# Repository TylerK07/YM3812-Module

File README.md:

# YM3812-Module
This code repository parallels a series of articles about a YM3812 module written on thingsmadesimple.com

With each new article, the functionality of the module will grow, and the associated code and schematics will be available here.

<hr/>

## Current Articles

### <a href='https://www.thingsmadesimple.com/2022/11/28/ym3812-part-1-register-basics/'>YM3812 Part 1: Register Basics</a>
Focuses on FM Synthesis basics, the YM3812's register map and electrically controlling the chip's pins.

### <a href='https://thingsmadesimple.com/2023/01/02/ym3812-part-2-face-reveal/'>YM3812 Part 2: FACE Reveal</a>
Introduces a basic implementation of the YM3812 circuit controlled by an AVR128DA28 microcontroller that we will build on in future articles. Think of it as a "Hello World" starting point that ensure the circuit works and that we can upload code to the microcontroller.

### <a href='https://www.thingsmadesimple.com/2023/01/21/ym3812-part-3-behind-the-code/'>YM3812 Part 3: Behind the Code</a>
Walks through the implementation of the YM3812 class used in Part 2 and describes how each of the register manipulation functions work.

### <a href='https://www.thingsmadesimple.com/2023/02/11/ym3812-part-4-midi-journey/'>YM3812 Part 4: MIDI Journey</a>
Adds a MIDI input to our schematic, and discusses how to translate MIDI note numbers into frequencies the YM3812 understands

### <a href='https://www.thingsmadesimple.com/2023/03/05/ym3812-part-5-midi-polyphony/'>YM3812 Part 5: MIDI Polyphony</a>
Adds Polyphony to our breadboard module, walking through a couple of algorithms in the process.

### <a href='https://www.thingsmadesimple.com/2023/04/29/ym3812-part-6-patches/'>YM3812 Part 6: Patches</a>
Revise the YM3812 class implementation to support more generic instrument definition

### <a href='https://www.thingsmadesimple.com/2023/05/13/ym3812-part-7-percussive-maintenance/'>YM3812 Part 7: Percussive Maintenance</a>
Add General MIDI drum support by linking different drum sounds to different notes on the keyboard

### <a href='https://www.thingsmadesimple.com/2023/05/30/ym3812-part-8-velocity-sensitivity/'>YM3812 Part 8: Velocity Sensitivity</a>
Add touch sensitivity to the module by selectively scaling the right operator levels

### <a href='https://www.thingsmadesimple.com/2023/07/28/ym3812-part-9-synth-card/'>YM3812 Part 9: SynthCard</a>
Turn that breadboard into a business card sized PCB!

### <a href='https://www.thingsmadesimple.com/2023/09/02/ym3812-part-10-pitch-bend/'>YM3812 Part 10: Pitch Bend</a>
Add pitch bend capabilities and shred on a YM3812

<hr/>

## Article Backlog:

### YM3812 Part ?: OPL2 in STEREO!
Add another YM3812 chip and some stereo effects for panning and detuning

### YM3812 Part ?: Adding a menu to swap patches
Add a TFT Screen and a Rotary Encoder so we can adjust patch assignments to MIDI channels

### YM3812 Part ?: Adjust Patch Properties
Add buttons and a menu system that lets us adjust patch settings individually

### YM3812 Part ?: Visualizing 2-OP envelopes
Add a graphical visualization that helps us interpret patch settings

### YM3812 Part ?: Virtual 4-OP Voices
Add support for virtual four-operator voices

and more...

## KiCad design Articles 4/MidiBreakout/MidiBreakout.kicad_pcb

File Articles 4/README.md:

### <a href=''>YM3812 Part 4: MIDI Journey</a>
This article introduces the circuitry and functionality necessary to implement MIDI on the YM3812 module. This article especially focuses on translating note frequencies between MIDI note codes and the block / F-Number properties used by the YM3812. To demonstrate how the translation function and basic MIDI handlers work, this code implements a monophonic midi algorithm that plays all incoming notes on channel zero of the YM3812.

<hr/>

### Schematic
The schematic folder includes adds MIDI functionality to the basic schematic used in articles 1-3.

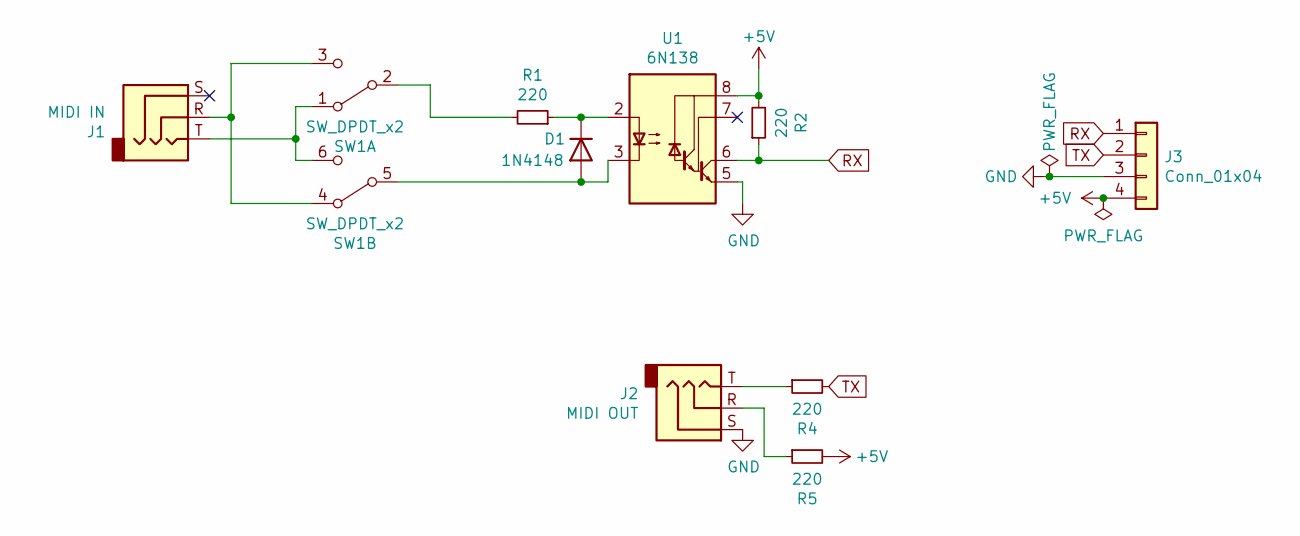
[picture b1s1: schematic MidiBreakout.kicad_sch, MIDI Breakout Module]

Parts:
D1: 1N4148; D_DO-35_SOD27_P7.62mm_Horizontal
J1: MIDI IN; PJ392_3.5MM_Vertical
J2: MIDI OUT; PJ392_3.5MM_Vertical
J3: Conn_01x04; PinHeader_1x04_P2.54mm_Vertical
R1, R2, R4, R5: 220; R_Axial_DIN0207_L6.3mm_D2.5mm_P7.62mm_Horizontal
SW1: SW_DPDT_x2; SW_E-Switch_EG1271_DPDT
U1: 6N138; DIP-8_W7.62mm_Socket_LongPads

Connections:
+5V: J3.4, R2.2, R5.2, U1.8 (VCC)
GND: J2.S, J3.3, U1.5 (GND)
unnamed: D1.1 (K), R1.1, U1.2 (C1)
unnamed: D1.2 (A), SW1.5 (B), U1.3 (C2)
unnamed: J1.R, SW1.3 (C), SW1.4 (A)
unnamed: J1.T, SW1.1 (A), SW1.6 (C)
unnamed: J2.R, R5.1
unnamed: J2.T, R4.1
unnamed: R1.2, SW1.2 (B)
RX: J3.1, R2.1, U1.6 (VO2)
TX: J3.2, R4.2

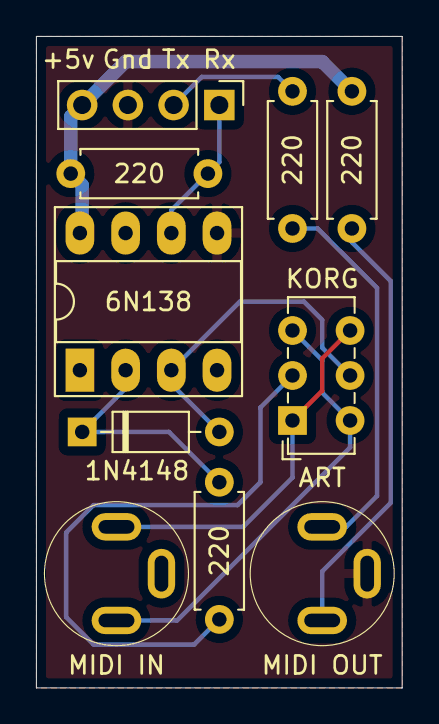
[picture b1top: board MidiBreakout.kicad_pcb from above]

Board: 2 copper layers, 20.3 x 36.2 mm, 10 parts (0 on the bottom side), 11 nets.

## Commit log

2022-12-26 Updating things to match the article and adding documentation
2022-12-26 Add schematic
2022-12-26 Adding Readme
2022-12-26 Updating the Readme file
2022-12-26 Editing the readme
2022-12-26 Moving files around
2023-01-30 Adding code for Article 4
2023-01-30 Added png of schematic
2023-03-05 Add files via upload
    Adding code for article 5
2023-03-05 Update README.md
    Add links for articles 4 and 5
2023-04-24 Adding code for article 6
    This code adds patch functionality to the module
2023-04-24 Adding op2 to instruments.h converter
2023-04-24 Add modules...
2023-04-24 Adding the rest of the modules...
2023-04-24 Adding readme for the instrument converter
2023-05-08 Tweaked Labels on the SCK/MOSI lines
2023-05-13 Adding Percussion Support
    Article 7 adds percussion support to the YM3812 EuroRack Module
2023-05-30 Article 8 Code
    Adding code for article 8 about velocity sensitivity.
2023-07-27 SynthCard
    Add SynthCard documentation
2023-09-01 Added Article 10 Pitch Bend
    This update includes all of the code associated with adding Pitch Bend to the YM3812 module
